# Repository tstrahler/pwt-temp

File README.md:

# Temperaturmessung für PWT
Dieses Projekt behandelt die Entwicklung einer Temperaturmessung zur Verwendung mit Plattenwärmetauschern (PWT). Die Temperaturmessung hat die Aufgabe den Temperaturgradienten über PWT zu erfassen, um so den Grad der Verschmutzung erfassen zu können.

* [Anforderungen](#anforderungen)
* [Realisierung der Temperaturmessung](#realisierung-der-temperaturmessung)
    * [Berührungslose Messung](#berührungslose-messung)
    * [Oberflächenmessung](#oberflächenmessung)
* [Entwicklung der Elektronik](#entwicklung-der-elektronik)

Eine Profilaufnahme eines solchen PWT ist im Folgenden dargestellt.

# Anforderungen
Um Verschmutzung mit ausreichender Genauigkeit erreichen zu können, sind Temperaturmessungen mit einem Abstand von ca. 10 mm erforderlich. Diese Temperaturmessungen müssen wie in der Abbildung in Y-Richtung gleichmäßig verteilt werden. Der zu messende Bereich entspricht in etwa einer Länge von 300 mm bis 800 mm. Eine Aufteilung in mehrere Messeinheiten bzw. Messkarten.

Die Genauigkeit der Temperaturmessung soll ≤1 °C betragen. Da jedoch ein Temperaturgradient zu messen ist, fällt die absolute Messabweichung in den Hintergund. Wichtiger ist eine homogene Messabweichung über alle Sensoren, sodass die Kalibrierung und Anpassung möglichst unkompliziert ist.

Da sich diese Wärmetauscher in feuchter und warmer Umgebung befinden, ist ein Wärmebereich zwischen -20 °C und 105 °C anzustreben. Die relative Luftfeuchtigkeit ist mit 70 % anzustreben.

# Realisierung der Temperaturmessung
Die Temperaturmessung kann nach unterschiedlichen Methoden durchgeführt werden. Im Folgenden wird zwischen der Berührungslosen und der Oberflächenmessung unterschieden. Beide Methoden habe Vor- und Nachteile.

## Berührungslose Messung
Die Berührungslose Messung basiert auf der Verwendung von Infrarot-Array-Sensoren. Das Grundprinzip dieser Sensoren basiert auf der Funktion bekannter Infrarot-Wärmebildsensoren. Diese Infrarot-Array-Sensoren besitzen jedoch eine weitaus geringere Auflösung.

Ein Produktbeispiel eines solchen Sensors ist der [AMG8834 von Panasonic](https://industrial.panasonic.com/cdbs/www-data/pdf/ADI8000/ADI8000C66.pdf). Dieser Sensor besitzt eine Auflösung von 8x8 Pixel und kann mittels I²C durch einen Mikrocontroller ausgelesen werden. Eine konzeptionelle Darstellung der Verwendung eines solchen Sensors ist in folgender Abbildung dargestellt.

Da der Sensor einen Bildwinkel von 60° besitzt, ist bei einer betrachteten Fläche mit 300 mm Seitenlänge eine Mindesthöhe von 260 mm erforderlich, um die gesamte Fläche mit einem Sensor abzudecken. Dabei kann eine Auflösung von max. 37.5 mm auf dem PWT erreicht werden. Diese Auflösung ist weit unter den geforderten 10 mm. Somit sind mehrere Sensoren erforderlich.

Die Genauigkeit des Sensor ist mit ±2.5 °C angegeben. Da jedoch ein Temperaturgradient zu erfassen ist, fällt die absolute Genauigkeit des Sensors in den Hintergrund. Weiterhin kann durch eine die Messabweichung des Sensors kalibriert und ausgeglichen werden.

Der Temperaturbereich der Umgebung wird mit -20 °C bis 80 °C angegeben. Da das Gerät jedoch nicht in direktem Kontakt mit dem PWT ist, wird dies als hinreichend angenommen. Ein Graph zur maximalen Umgebungsfeuchtigkeit ist im Datenblatt gegeben. Die maximal zu messende Temperatur ist mit 100 °C angegeben.

Aufgrund der metalischen Oberflächenbeschaffenheit des PWT, ist eine direkte Messung mittels Infrarot-Array-Sensors voraussichtlich nicht möglich. Durch ein aufkleben eines Papierstickers kann dieses Problem jedoch gelöst werden.

Der Preis eines solchen Sensors ist, abhängig vom Distributor, mit 30 € anzunehmen. Da mehrere Sensoren zur Erfassung der Mindestfläche erforderlich sind, ist sind Kosten von 60 € pro Sensor aufwärts anzunehmen.

## Oberflächenmessung
Eine weitere Methode zur Messung der Oberflächentemperatur des PWT, ist die Messung durch Kontakt zur Oberfläche. Dies kann entweder durch integrierte Lösungen oder durch Oberflächensensoren durchgeführt werden. Da Oberflächensensoren mit relativ hohen hosten und Montageaufwand verbunden sind, wird diese Möglichkeit nicht weiter verfolgt.

Integrierte Lösungen sind eine wesentlich kostengüstigere Methode zur Aufnahme von Temperaturen. Diese integrierten Temperaursensoren kommen jedoch mit dem Nachteil, dass sie in direktem Kontakt mit der unterliegenden Platine sind. Dies führt zu einer Beeinflussung der Messungen mehrerer Sensoren. Durch die Schaffung eines Überganges mit geringem Wärmewiderstand, lässt sich dieser Effekt jedoch etwas redizieren. So können die Sensoren beispielweise durch eine kleine Menge Wärmeleitkleber mit dem PWT verklebt werden. Es existieren weitere gleichartige Methoden zur Lösung dieses Problems.

Zu Beginn werden Sensoren mit digitaler Kommunikation untersucht. Diese sind mit verschiedenen Schnittstellen erhältlich. Darunter SPI, I²C und 1-Wire. Da bei dieser Anwendung eine großzahl an Sensoren erforderlich ist, ist die Verwendung von 1-Wire mit der wenigsten "Zusatzhardware" verbunden.

Sensoren welche über die 1-Wire Schnittstelle verfügen, können aufgrund ihrer itegrierten 64-Bit Adresse quasi endlos oft mit der selben Datenleitung verbunden werden. Dies ist in der vorliegenden Anwendung deutlich von Vorteil. Diese Sensoren bringen jedoch den Nachteil mit, dass sie relativ teuer sind, oder nicht auf dem gesamten Temperaturbereich die geforderte Genauigkeit von ≤1 °C besitzen. Durch vorheriges Kalibrieren und Ausgleichen des Messfehlers kann dem jedoch entgegen gekommen werden.

Sensoren mit 1-Wire Schnittstelle sind z.B. der bekanntere [DS18B20](https://datasheets.maximintegrated.com/en/ds/DS18B20.pdf) von Maxim. Dieser Sensor erfüllt zwar die Anforderung an die Messgenauigkeit, ist mit einem Preis von ca. 5,00 € sehr teuer. Ein weiteres Produkt von Maxim ist der [MAX31820](https://datasheets.maximintegrated.com/en/ds/MAX31820.pdf). Dieser Sensor ist mit 3,00 € wesentlich günstiger, besitzt jedoch im geforderten Temperaturbereich eine Messgenauigkeit von ±2 °C.

# Entwicklung der Elektronik
Da sich wie zuvor beschreiben für Infrarot-Array-Sensoren entschieden würde, wird die Architektur der Elektronik dementsprechend aufgebaut. Zu Beginn sind die Anforderungen an die Elektronik zu stellen.

## Anforderungen an die Elektronik
Die Anforderungen an die Elektronik unterscheiden sich von den Anforderungen an das Gesamtsystem. So wurden folgenden Anforderungen definiert:
* Modularität einzelner Messplatinen für unterschiedlich große PWT
* Geringer Verdrahtungsaufwand
* Wenig bis keine Konfiguration erforderlich
* Programmierung und Kalibrierung der Messplatinen schnell möglich
* Speicherung ohne weitere Geräte
* Großer Bereich der Versorgungsspannung

Aus diesen Anforderungen geht die unten abgebildete Grundarchitektur des gesammten Messystems hervor.

Die Temperatursensoren befinden sich jeweils auf einer Messplatine, um den Abstand dieser der Situation anzupassen. Da die AMG8834 lediglich zwei verschiedene Adressen besitzen können, ist auf jeder ein Mikrocontroller erforderlich. Dieser Mikrocontroller ist für die Kommunikation des Master mit den einzelnen AMG8834 zuständig.

Datenspeicherung sowie Versorgung des Systems wird durch das Master-Gerät durchgeführt. Als Speichermedium wird eine SD-Karte verwendet. Als günstigen Bereich der Spannungsversorgung wird 5 V bis 30 V verwendet.

Die Verbindung aller Geräte, zur Kommunikation sowie Versorgung, wird durch Flachbandkabel realisiert. Diese Flachbandkabel werden mittels [2.54 mm Pfostensteckverbinder](https://www.samtec.com/products/tst-103-01-g-d) mit der Platine verbunden. Um Crosstalk zwischen den I²C Leitungen zu minimieren, werden jeweils zwei Masse bzw. Versorgungssignale übertragen. So sind Steckverbinder mit 6 Kontakten erforderlich.

Programmierung, Kalibrierung und Justierung der Messgeräte wird durch eine USB-Schittstelle durchgeführt.

## Architektur der Messplatinen
Kern der Messplatinen bildet ein Mikrocontroller. Auf Grund der aktuell beschränkten Verfügbarkeit von Halbleiterbauteilen, wird sich für den [Raspberry Pi RP2040](https://datasheets.raspberrypi.com/rp2040/rp2040-datasheet.pdf) entschieden.
Da sich mehrere dieser Geräte an einem I²C-Bus befinden, ist eine Adresswahl erforderlich. Die Adresse der Individuellen Messplatinen kann durch einen DIP-Schalter in den Bereich von 0 und 15 gewählt werden.

Ein Rendering der Messplatine ist im Folgenen zu sehen.

## Architektur des Master-Gerätes
Es wurde sich dazu entschieden zwei LED-Indikatoren auf dem Master-Gerät zu verbauen. Ein Indikator zeit die funktionierende Spannungsversorgung von 3.3 V an. Dieser ist grün und leuchtet durchgegend. Zwei weitere Indikatoren dienen der Anzeige des Betriebszustands und sind grün und rot. Es sind folgende Anzeigemodi dieser Status-Indikatoren möglich:

## Kommunikationsschnittstelle
[NXP Application Node inkl. Auslegung von langen I²C Bussen](https://www.nxp.com/docs/en/user-guide/UM10204.pdf)

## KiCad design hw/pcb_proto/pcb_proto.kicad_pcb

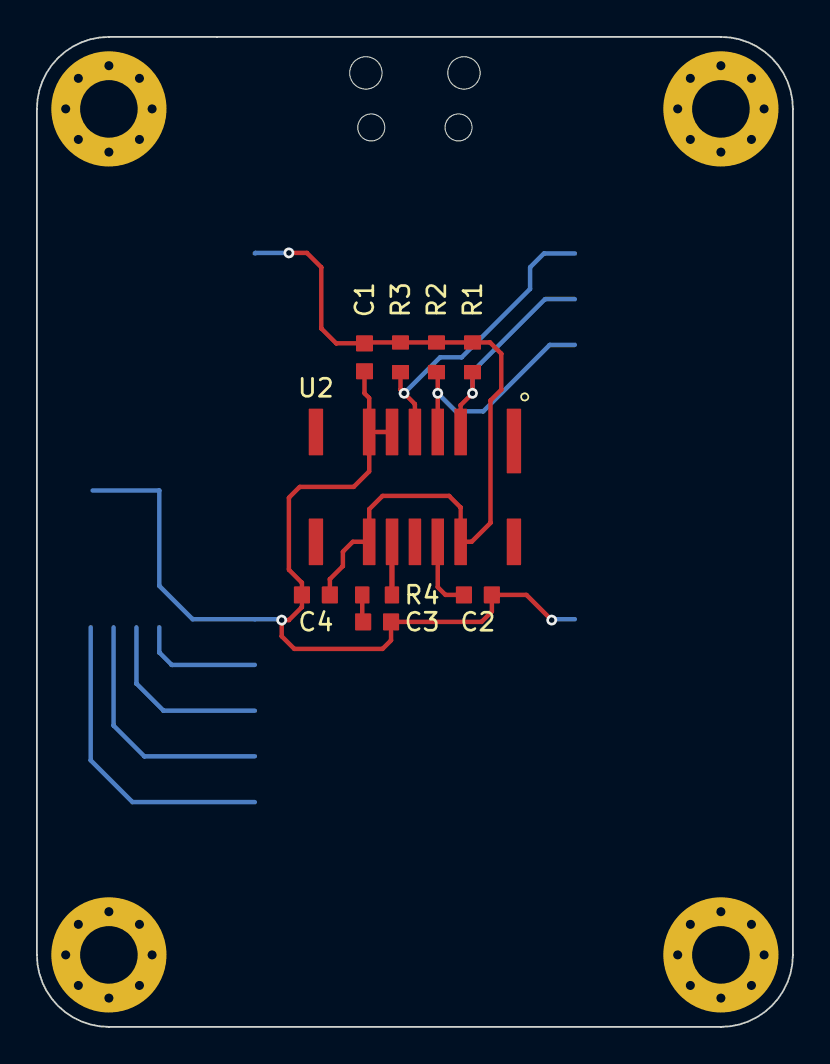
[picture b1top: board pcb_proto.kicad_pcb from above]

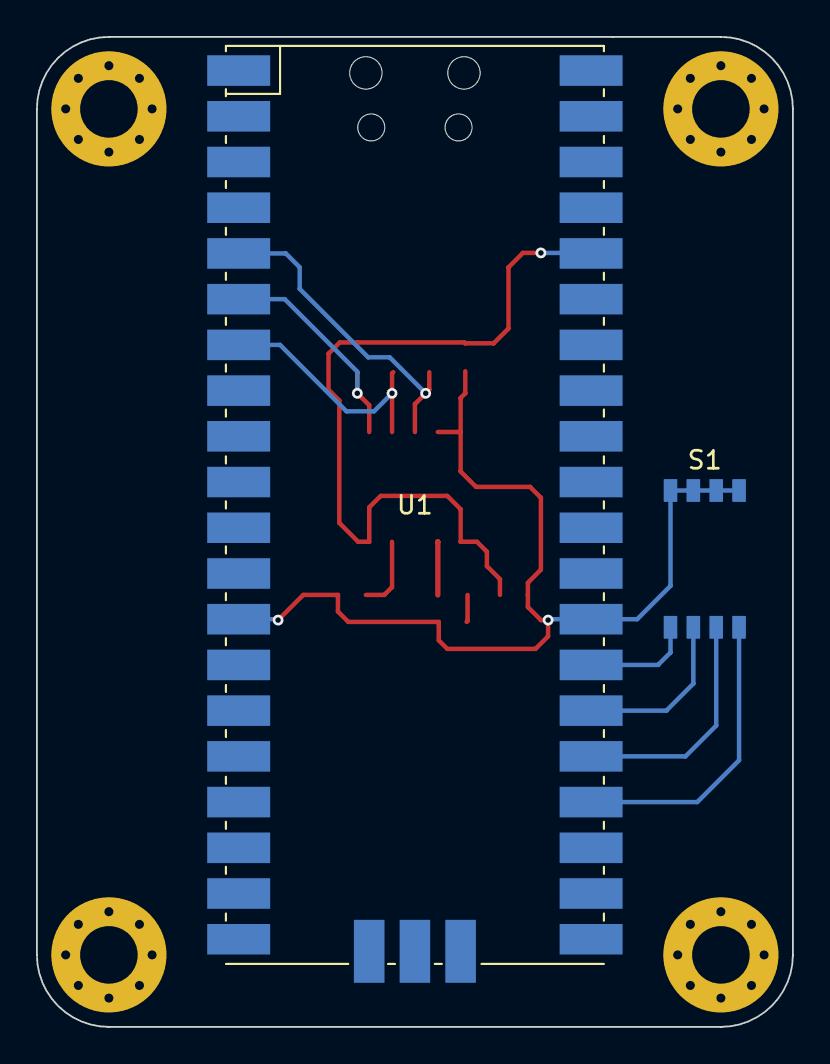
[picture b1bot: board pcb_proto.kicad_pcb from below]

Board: 2 copper layers, 42.0 x 55.0 mm, 15 parts (2 on the bottom side), 12 nets.

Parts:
C1, C4: 10u; C_0603
C2, C3: 1u; C_0603
H1, H2, H3, H4: MountingHole; MountingHole_3.2mm_M3_Pad_Via
R1, R2, R3: 10k; R_0603
R4: 20R; R_0603
S1: MECH_SW_DIP4_SMD
U1: MECH_RPIPICO_SMD
U2: IC_AMG8834

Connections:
+3V3: C1.1, C4.1, R1.1, R2.1, R3.1, U1.36 (3V3), U2.9 (VDD), U2.13 (VPP)
/AVDD: R4.2, U2.10 (AVDD-PC)
/DVDD: C2.1, U2.12 (DVDD-PC)
/INT: R3.2, U1.5 (GPIO3), U2.4 (INT)
/SCL: R2.2, U1.7 (GPIO5), U2.3 (SCL)
/SDA: R1.2, U1.6 (GPIO4), U2.2 (SDA)
/SW0: S1.1, U1.27 (GPIO21)
/SW1: S1.2, U1.26 (GPIO20)
/SW2: S1.3, U1.25 (GPIO19)
/SW3: S1.4, U1.24 (GPIO18)
GND: C1.2, C2.2, C3.2, C4.2, S1.5, S1.6, S1.7, S1.8, U1.13 (GND), U1.28 (GND), U2.5 (AD_SELECT), U2.6 (GND)
unnamed: C3.1, R4.1

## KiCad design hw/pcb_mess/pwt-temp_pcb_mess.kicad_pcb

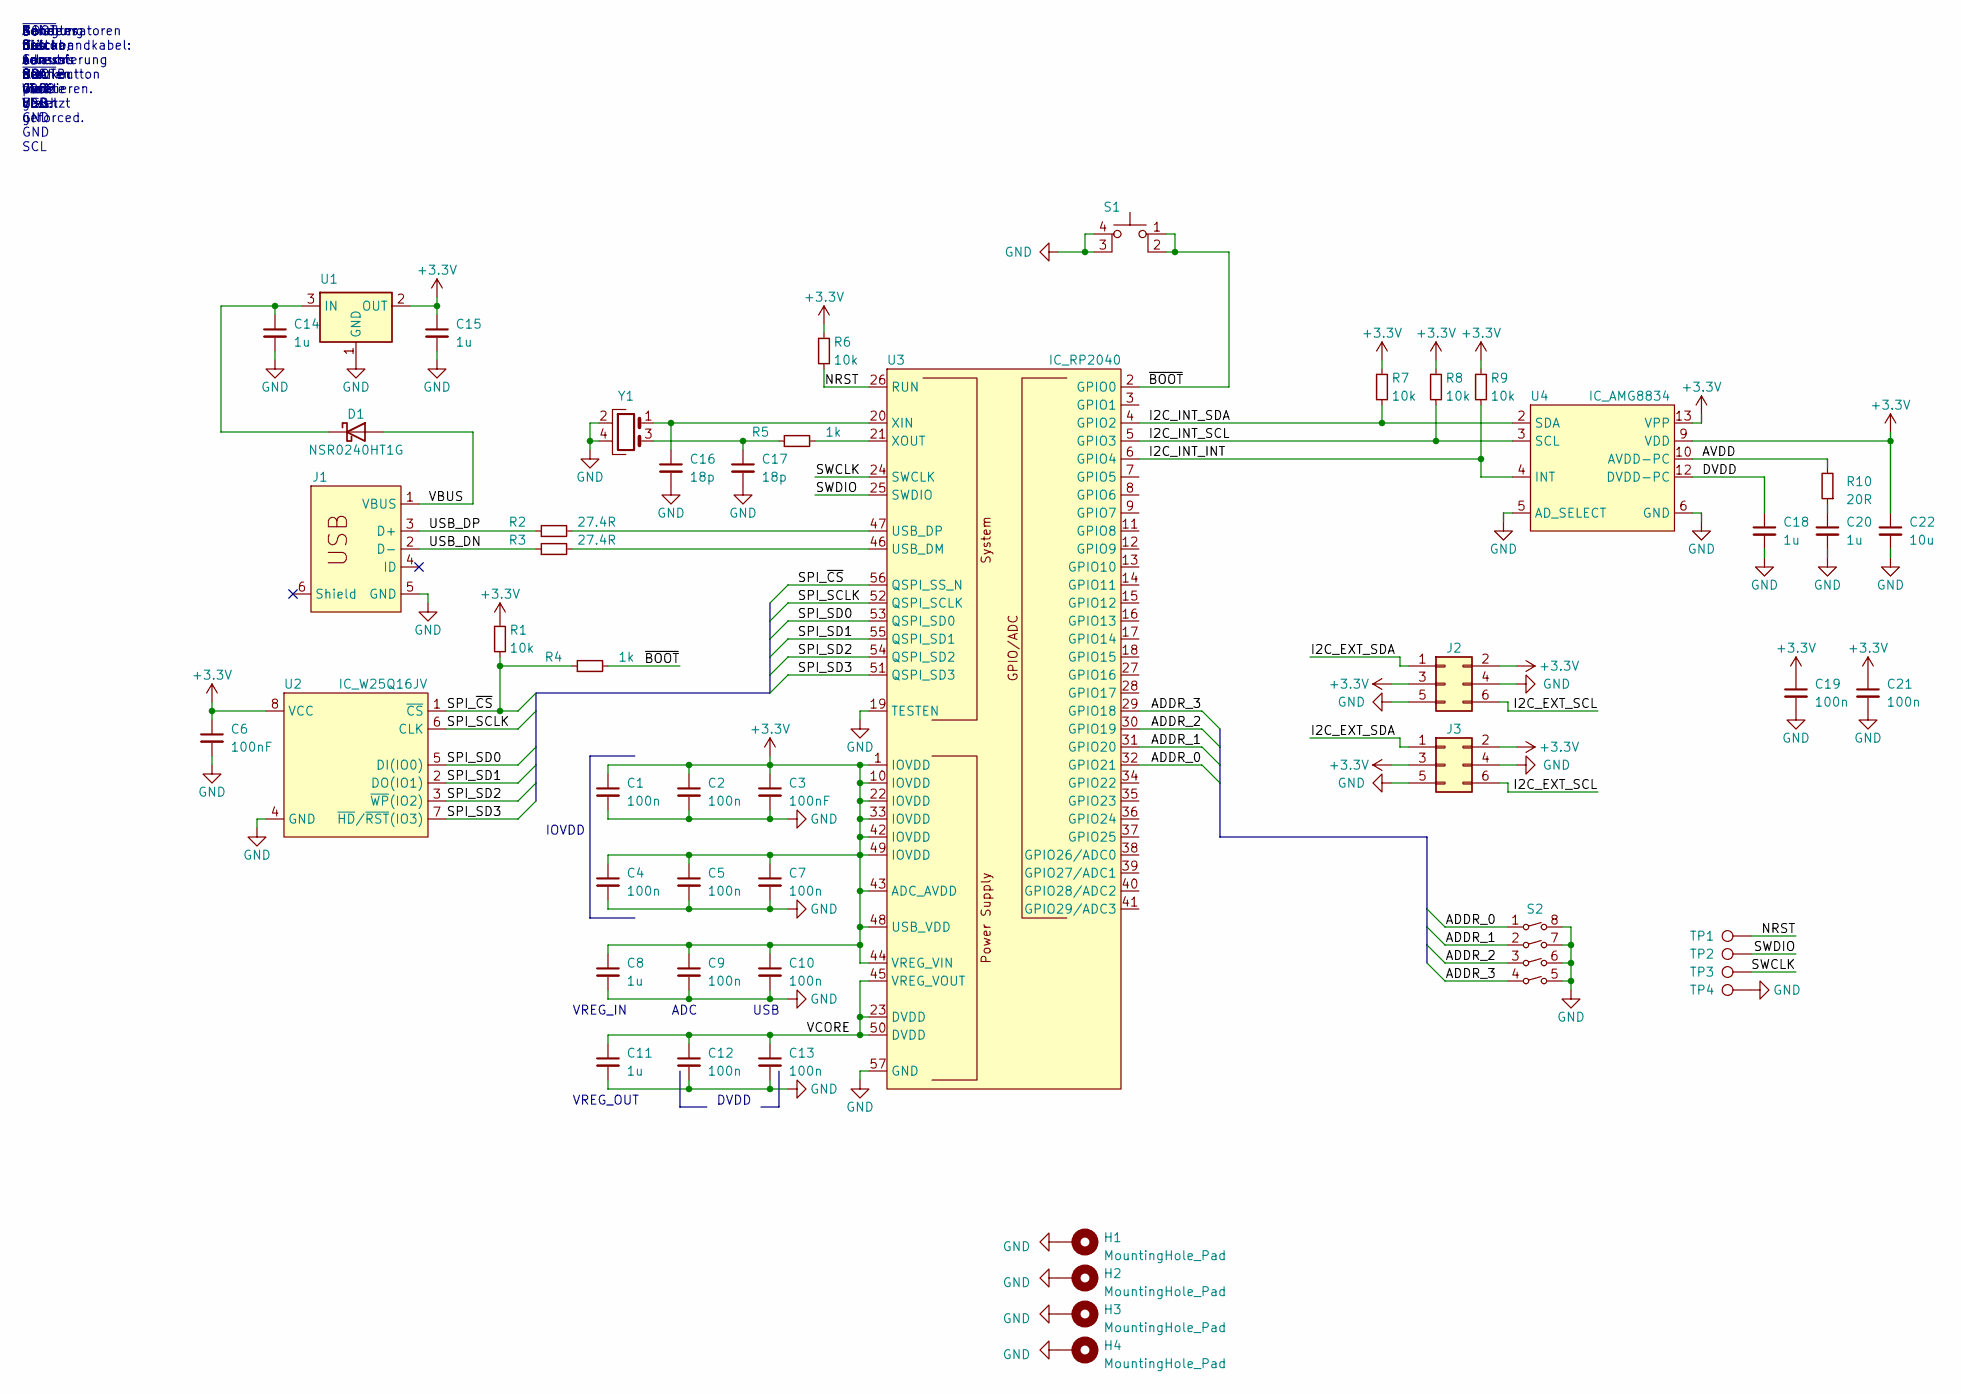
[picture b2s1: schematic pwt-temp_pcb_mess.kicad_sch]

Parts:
C1, C2, C4, C5, C7, C9, C10, C12, C13, C19, C21: 100n; C_0603
C3, C6: 100nF; C_0603
C8, C11, C14, C15, C18, C20: 1u; C_0603
C16, C17: 18p; C_0603
C22: 10u; C_0603
D1: D_SCH_40V_0.25A; SOD_323
H1, H2, H3, H4: MountingHole_Pad; MountingHole_3.2mm_M3_Pad_Via
J1: CON_USB_B_MINI
J2, J3: CON_PH_2.54MM_2x3_VERT
R1, R6, R7, R8, R9: 10k; R_0603
R2, R3: 27.4R; R_0603
R4, R5: 1k; R_0603
R10: 20R; R_0603
S1: MECH_BTN_SMD_SMALL
S2: MECH_SW_DIP4_SMD
TP1, TP2, TP3, TP4: TestPoint; TestPoint_Pad_D1.5mm
U1: PMIC_LDO_3V3_0.2A; SOT_23_3
U2: IC_W25Q16JV
U3: IC_RP2040
U4: IC_AMG8834
Y1: OSC_ABM10-12.000MHZ; OSC_ABM10

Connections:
+3V3: C1.1, C2.1, C3.1, C4.1, C5.1, C6.1, C7.1, C8.1, C9.1, C10.1, C15.1, C19.1, C21.1, C22.1, J2.2, J2.3, J3.2, J3.3, R1.1, R6.1, R7.1, R8.1, R9.1, U1.2 (OUT), U2.8 (VCC), U3.1 (IOVDD), U3.10 (IOVDD), U3.22 (IOVDD), U3.33 (IOVDD), U3.42 (IOVDD), U3.43 (ADC_AVDD), U3.44 (VREG_VIN), U3.48 (USB_VDD), U3.49 (IOVDD), U4.9 (VDD), U4.13 (VPP)
/ADDR_0: S2.1, U3.32 (GPIO21)
/ADDR_1: S2.2, U3.31 (GPIO20)
/ADDR_2: S2.3, U3.30 (GPIO19)
/ADDR_3: S2.4, U3.29 (GPIO18)
/AVDD: R10.2, U4.10 (AVDD-PC)
/DVDD: C18.1, U4.12 (DVDD-PC)
/I2C_EXT_SCL: J2.6, J3.6
/I2C_EXT_SDA: J2.1, J3.1
/I2C_INT_INT: R9.2, U3.6 (GPIO4), U4.4 (INT)
/I2C_INT_SCL: R8.2, U3.5 (GPIO3), U4.3 (SCL)
/I2C_INT_SDA: R7.2, U3.4 (GPIO2), U4.2 (SDA)
/NRST: R6.2, TP1.1, U3.26 (RUN)
/SPI_SCLK: U2.6 (CLK), U3.52 (QSPI_SCLK)
/SPI_SD0: U2.5 (DI(IO0)), U3.53 (QSPI_SD0)
/SPI_SD1: U2.2 (DO(IO1)), U3.55 (QSPI_SD1)
/SPI_SD2: U2.3 (~WP(IO2)), U3.54 (QSPI_SD2)
/SPI_SD3: U2.7 (~HD/~RST(IO3)), U3.51 (QSPI_SD3)
/SPI_~CS: R1.2, R4.1, U2.1 (~CS), U3.56 (QSPI_SS_N)
/SWCLK: TP3.1, U3.24 (SWCLK)
/SWDIO: TP2.1, U3.25 (SWDIO)
/USB_DN: J1.2 (D-), R3.1
/USB_DP: J1.3 (D+), R2.1
/VBUS: D1.2 (A), J1.1 (VBUS)
/VCORE: C11.1, C12.1, C13.1, U3.23 (DVDD), U3.45 (VREG_VOUT), U3.50 (DVDD)
/~BOOT: R4.2, S1.1, S1.2, U3.2 (GPIO0)
GND: C1.2, C2.2, C3.2, C4.2, C5.2, C6.2, C7.2, C8.2, C9.2, C10.2, C11.2, C12.2, C13.2, C14.2, C15.2, C16.2, C17.2, C18.2, C19.2, C20.2, C21.2, C22.2, H1.1, H2.1, H3.1, H4.1, J1.5 (GND), J2.4, J2.5, J3.4, J3.5, S1.3, S1.4, S2.5, S2.6, S2.7, S2.8, TP4.1, U1.1 (GND), U2.4 (GND), U3.19 (TESTEN), U3.57 (GND), U4.5 (AD_SELECT), U4.6 (GND), Y1.2, Y1.4
unnamed: C17.1, R5.1, Y1.3
unnamed: C20.1, R10.1
unnamed: C14.1, D1.1 (K), U1.3 (IN)
unnamed: R3.2, U3.46 (USB_DM)
unnamed: R2.2, U3.47 (USB_DP)
unnamed: C16.1, U3.20 (XIN), Y1.1
unnamed: R5.2, U3.21 (XOUT)

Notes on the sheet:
Bei drücken von ~{BOOT}Button wird Flash geforced.
Kondensatoren nah an Stecker platzieren.
~{BOOT} Button, erlaubt flashen via USB.
Adr. des Sensors auf 0x68 gesetzt
Schalter für Adressierung der Geräte
Belegung Flachbandkabel: SDA VDD VDD GND GND SCL
VREG_OUT
ADC
IOVDD
USB
VREG_IN
DVDD

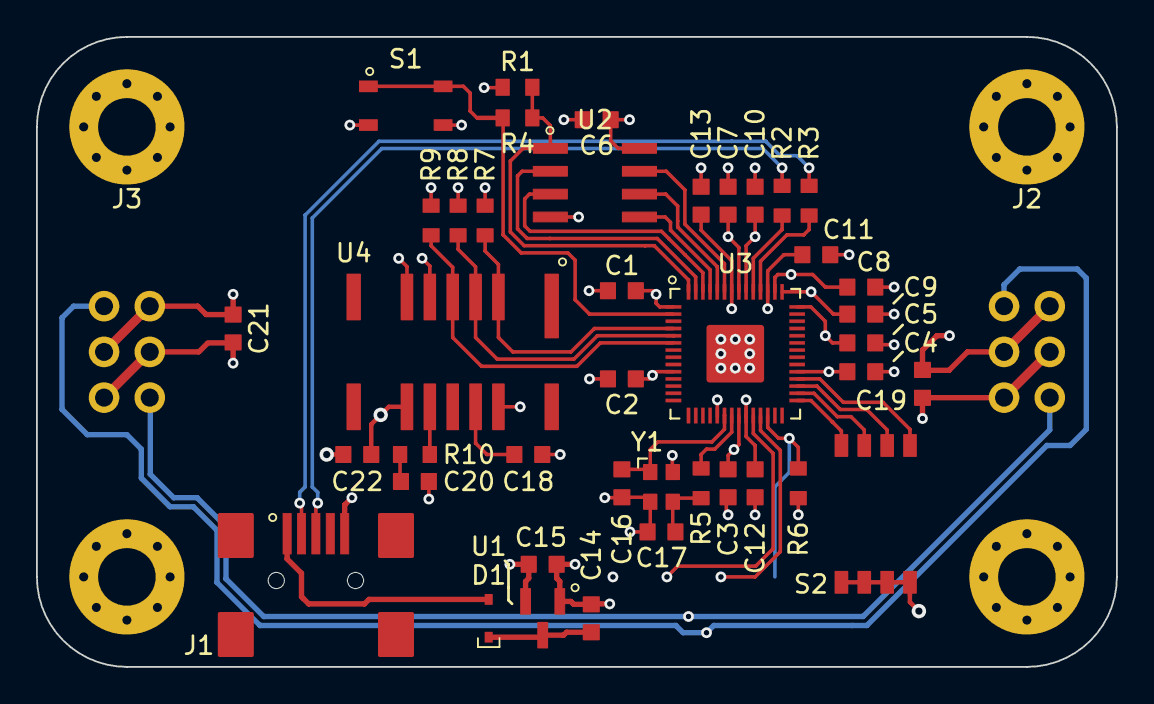
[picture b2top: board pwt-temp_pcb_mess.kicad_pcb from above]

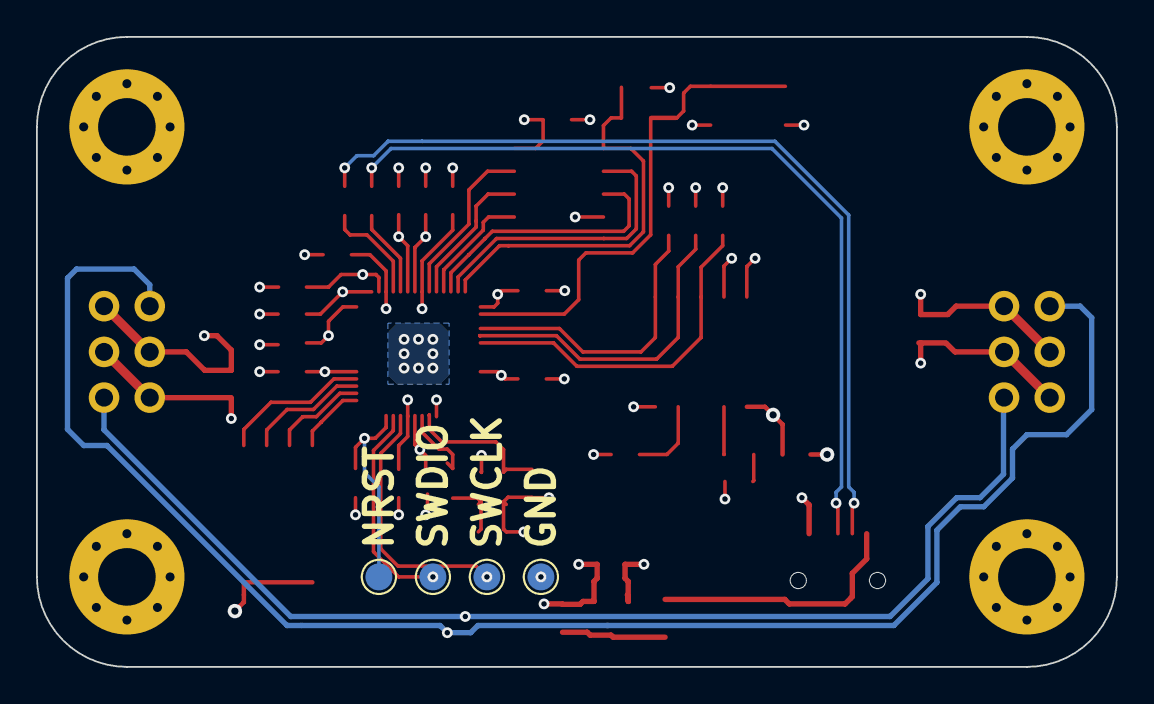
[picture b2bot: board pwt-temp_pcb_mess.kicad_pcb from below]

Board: 4 copper layers, 60.0 x 35.0 mm, 51 parts (4 on the bottom side), 34 nets.

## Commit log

2022-01-30 Initial Push
2022-01-30 Dokumentation und Ordnerstruktur
2022-01-30 Symbol und Footprint für IC_AMG8834 hinzugefügt
2022-01-31 RP2040 Symbol & Footprint hinzugefügt
2022-01-31 Updated .gitignore
2022-01-31 Updates wiring
2022-02-01 Flash Symbol & Footprint hinzugefügt
2022-02-01 ABM10 Quartz Footprint & Symbol hinzugefügt
2022-02-03 Hinzufügen von Steckern und Schaltreglermodul
2022-02-04 Schaltplan begonnen
2022-02-08 Flash hinzugefügt
2022-02-08 Boot Button hinzugefügt
2022-02-08 Dokumentation
2022-02-11 Schaltplan Messplatine fertig
2022-02-13 Layout & Schaltplan erzeugt
2022-02-13 Schaltplan hinzugefügt
2022-02-14 Finished Layout
2022-02-16 Modified .gitignore
2022-02-17 Layout fertiggestellt
2022-02-25 Added rendering
2022-02-25 Added Rendeirng file type
2022-04-26 pwt project updated
2022-06-26 Created firmware & python IF
